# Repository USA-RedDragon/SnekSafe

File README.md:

# SnekSafe

Keep your snek safe by controlling temperature and lighting.

## Assembled v1.1 Board

## Board Renders

## Schematic

## Board Layout

## Site Images

## Parts not in the BOM that you might need

- 14AWG Silicone Wire - <https://www.amazon.com/dp/B089CRKSNN>
- Spade connectors for 14AWG - <https://www.amazon.com/dp/B08BZ972B5>
- 24AWG 4-conductor wire - <https://www.amazon.com/dp/B0BYDTCZ61>
- JST XH crimpers
- Heat shrink
- A 3d printer

## Cost

The one-off BOM cost, assuming you have spade connectors and 14AWG wire on hand is $121.25.

## On ESP32 choice

I chose the official ESP32-DevKitC-32E (ESP32-DevKitC V4) board due to quality. For some reason, on a cheaper NodeMCU ESP32S I was able to scan less WiFi networks and got a lower effective range.

## Premade Carts

A few items, such as the C13 AC cord, the C14 AC plug, and the panel mount AC outlets must be sourced on your own, as DigiKey and Mouser don't sell these commonly.

### JST XH Plug Parts

Mouser doesn't stock these: <https://www.digikey.com/short/1hzrmn3b>

### Mouser

<https://www.mouser.com/ProjectManager/ProjectDetail.aspx?AccessID=c3308da5f2>

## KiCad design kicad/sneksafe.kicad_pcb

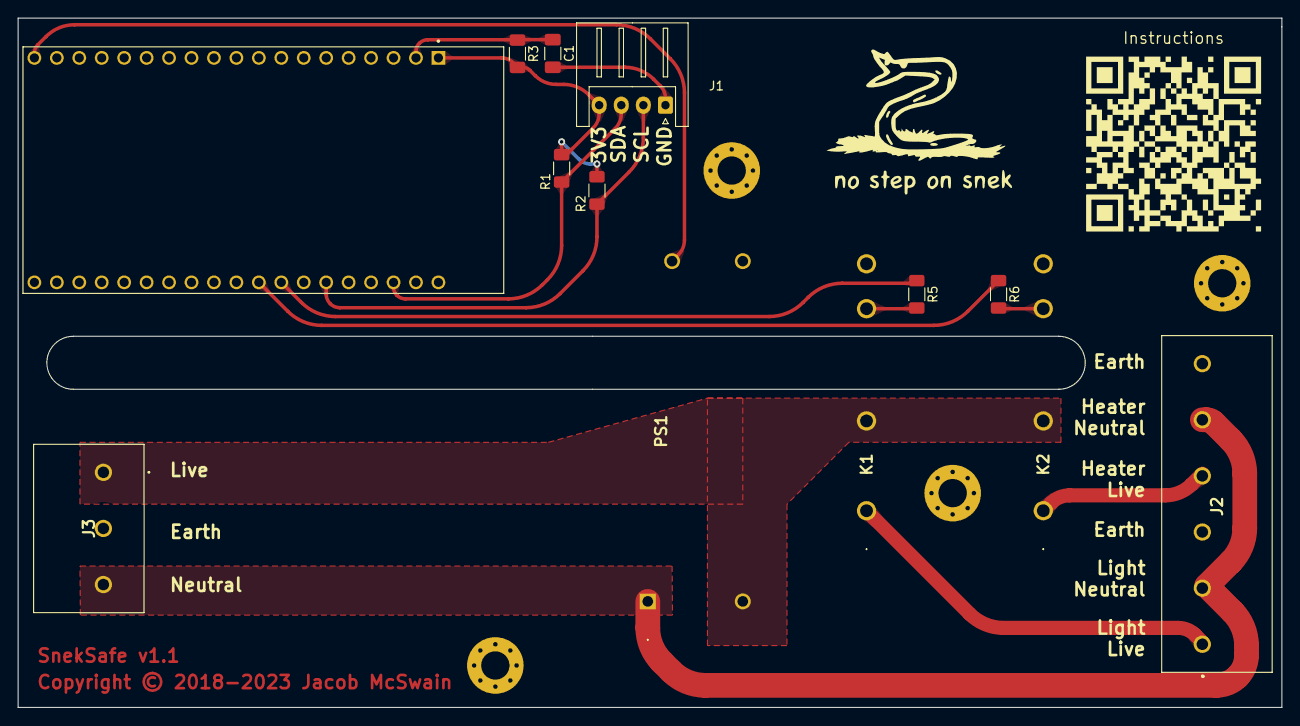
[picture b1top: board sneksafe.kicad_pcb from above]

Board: 2 copper layers, 143.0 x 78.0 mm, 18 parts (0 on the bottom side), 15 nets.

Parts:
C1: 1u; C_1206_3216Metric_Pad1.33x1.80mm_HandSolder
J1: S4B-XH-A(LF)(SN); JST_XH_S4B-XH-A_1x04_P2.50mm_Horizontal
J2: Screw_Terminal_01x06; 1713969
J3: Screw_Terminal_01x03; 1714968
K1, K2: CPC40055ST
MH1, MH2: MountingHole_3.2mm_M3_Pad_Via
MH3, MH4: MountingHole_Pad; MountingHole_3.2mm_M3_Pad_Via
PS1: RAC10E-05SK_277; RAC10E05SK277
QR*****: Instructions; rickroll
R1, R2: 2.4k; R_1206_3216Metric_Pad1.30x1.75mm_HandSolder
R3: 10k; R_1206_3216Metric_Pad1.30x1.75mm_HandSolder
R5, R6: 422; R_1206_3216Metric_Pad1.30x1.75mm_HandSolder
U1: ESP32-DEVKITC-32D; MODULE_ESP32-DEVKITC-32D

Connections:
+3.3V: J1.4, R1.2, R2.2, R3.2, U1.J2-1 (3V3)
+5V: PS1.4 (+VOUT), U1.J2-19 (EXT_5V)
AC_N_IN: J2.2, J2.5, J3.3, PS1.1 (VAC_IN_(N))
AC_P_IN: J3.1, K1.2 (AC_LOAD_2), K2.2 (AC_LOAD_2), PS1.2 (VAC_IN_(L))
Earth: MH3.1, MH4.1
GND: C1.2, J1.1, K1.4 (-_LED), K2.4 (-_LED), PS1.3 (-VOUT), U1.J2-14 (GND1), U1.J3-1 (GND3), U1.J3-7 (GND2)
HEAT_AC_P: J2.4, K2.1 (AC_LOAD_1)
HEAT_EN: R6.1, U1.J3-9 (IO18)
HEAT_LED_P: K2.3 (+_LED), R6.2
LIGHT_AC_P: J2.1, K1.1 (AC_LOAD_1)
LIGHT_EN: R5.1, U1.J3-8 (IO19)
LIGHT_LED_P: K1.3 (+_LED), R5.2
unnamed: C1.1, R3.1, U1.J2-2 (EN)
SCL: J1.3, R1.1, U1.J3-3 (IO22)
SDA: J1.2, R2.1, U1.J3-6 (IO21)

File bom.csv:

"Id";"Designator";"Footprint";"Quantity";"Designation";"Supplier and ref";
1;"R1,R2";"R_1206_3216Metric_Pad1.30x1.75mm_HandSolder";2;"2.4k";;;
2;"U1";"MODULE_ESP32-DEVKITC-32D";1;"ESP32-DEVKITC-32D";;;
3;"R3";"R_1206_3216Metric_Pad1.30x1.75mm_HandSolder";1;"10k";;;
4;"R6,R5";"R_1206_3216Metric_Pad1.30x1.75mm_HandSolder";2;"422";;;
5;"J2";"1713969";1;"Screw_Terminal_01x06";;;
6;"PS1";"RAC10E05SK277";1;"RAC10E-05SK_277";;;
7;"J1";"JST_XH_S4B-XH-A_1x04_P2.50mm_Horizontal";1;"BME280";;;
8;"K1,K2";"CPC40055ST";2;"CPC40055ST";;;
9;"C1";"C_1206_3216Metric_Pad1.33x1.80mm_HandSolder";1;"1u";;;
10;"J3";"1714968";1;"Screw_Terminal_01x03";;;

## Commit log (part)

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2023-07-07 chore(deps): update dependency vite to ^4.4.2
2023-07-07 chore(deps): update dependency semver to ^7.5.4
2023-07-10 fix(deps): update dependency primevue to ^3.30.0
2023-07-10 chore(deps): update node.js to v20.4
2023-07-11 chore(deps): update dependency vite to ^4.4.3
2023-07-11 chore(deps): update dependency prettier to v3
2023-07-14 chore(deps): update dependency vite to ^4.4.4
2023-07-14 fix(deps): update dependency primevue to ^3.30.1
2023-07-14 chore(deps): update dependency eslint to ^8.45.0
2023-07-20 chore(deps): update dependency sass to ^1.64.0
2023-07-20 fix(deps): update dependency primevue to ^3.30.2
2023-07-21 chore(deps): update dependency vite to ^4.4.6
2023-08-01 chore(deps): update dependency chart.js to ^4.3.2
2023-08-01 chore(deps): update dependency sass to ^1.64.2
2023-08-01 chore(deps): update dependency eslint to ^8.46.0
2023-08-01 chore(deps): update node.js to v20.5
2023-08-01 chore(deps): update dependency eslint-plugin-vue to ^9.16.1
2023-08-02 fix(deps): update dependency primevue to ^3.31.0
2023-08-02 chore(deps): update font awesome to ^6.4.2
2023-08-03 chore(deps): update dependency chart.js to ^4.3.3
2023-08-08 chore(deps): update dependency @rushstack/eslint-patch to ^1.3.3
2023-08-08 chore(deps): update dependency eslint-plugin-cypress to ^2.13.4
2023-08-08 chore(deps): update dependency eslint-plugin-cypress to ^2.14.0
2023-08-09 chore(deps): update dependency eslint-plugin-vue to ^9.17.0
2023-08-10 chore(deps): update dependency sass to ^1.65.1
2023-08-11 fix(deps): update dependency primevue to ^3.32.0
2023-08-11 chore(deps): update dependency eslint to ^8.47.0
2023-08-17 chore(deps): update dependency @vitejs/plugin-vue to ^4.3.1
2023-08-17 chore(deps): update dependency sass to ^1.66.0
2023-08-18 fix(deps): update dependency primevue to ^3.32.1
2023-08-19 chore(deps): update dependency sass to ^1.66.1
2023-08-21 chore(deps): update dependency @vitejs/plugin-vue to ^4.3.2
2023-08-22 chore(deps): update dependency @vitejs/plugin-vue to ^4.3.3
2023-08-24 chore(deps): update dependency chart.js to ^4.4.0
2023-08-25 fix(deps): update dependency @vuelidate/validators to ^2.0.4
2023-08-25 chore(deps): update dependency eslint to ^8.48.0
2023-08-26 fix(deps): update dependency axios to ^1.5.0
2023-08-29 chore(deps): update dependency @vitejs/plugin-vue to ^4.3.4
2023-08-31 chore(deps): update dependency platformio/platform-espressif32 to v6.4.0
2023-09-01 fix(deps): update dependency primevue to ^3.33.0
2023-09-05 chore(deps): update node.js to v20.6
2023-09-06 chore(deps): update actions/checkout action to v4
2023-09-06 chore(deps): update dependency @vue/eslint-config-prettier to v8
2023-09-08 fix(deps): update dependency primevue to ^3.34.1
2023-09-08 chore(deps): update dependency eslint to ^8.49.0
2023-09-14 chore(deps): update dependency sass to ^1.67.0
2023-09-15 chore(deps): update dependency @rushstack/eslint-patch to ^1.4.0
2023-09-20 chore(deps): update node.js to v20.7
2023-09-21 chore(deps): update dependency sass to ^1.68.0
2023-09-21 chore(deps): update dependency start-server-and-test to ^2.0.1
2023-09-22 renovate.json: add versioning to regex
2023-09-22 platformio.ini: update versioning
2023-09-22 renovate: add extract version template
2023-09-22 Kibot: don't allow blind vias
2023-09-22 kibot: fix cache
2023-09-22 kicad: fixups
2023-09-22 ci: add kibot
2023-09-22 kicad: fix DRC silkscreen clipping
2023-09-22 chore(deps): update dependency esphome/espasyncwebserver to v3.1.0
2023-09-22 chore(deps): update dependency bblanchon/arduinojson to v6.21.3
2023-09-22 chore(deps): update dependency powerbroker2/ardupid to v0.2.1
2023-09-22 chore(deps): update inti-cmnb/kibot action to v2
2023-09-22 renovate: try to fixup some odd versioning
2023-09-22 v1.1.4
2023-09-22 fix(deps): update dependency vue-router to ^4.2.5
2023-09-23 chore(deps): update dependency eslint to ^8.50.0
2023-09-26 fix(deps): update dependency primevue to ^3.35.0
2023-09-26 fix(deps): update dependency axios to ^1.5.1
2023-09-29 chore(deps): update node.js to v20.8
2023-10-01 chore(deps): update dependency @rushstack/eslint-patch to ^1.5.1
2023-10-02 chore(deps): update dependency @vitejs/plugin-vue to ^4.4.0
2023-10-03 chore(deps): update dependency vite to ^4.4.10
2023-10-05 chore(deps): update dependency vite to ^4.4.11
2023-10-06 chore(deps): update dependency eslint to ^8.51.0
2023-10-09 chore(deps): update ghcr.io/inti-cmnb/kicad7_auto:latest docker digest to 0a5e846
2023-10-10 chore(deps): update dependency sass to ^1.69.1
2023-10-10 chore(deps): update dependency sass to ^1.69.2
2023-10-11 fix(deps): update dependency primevue to ^3.36.0
2023-10-12 chore(deps): update dependency sass to ^1.69.3
2023-10-17 chore(deps): update dependency sass to ^1.69.4
2023-10-18 chore(deps): update ghcr.io/inti-cmnb/kicad7_auto:latest docker digest to 595bdcc
2023-10-18 fix(deps): update dependency primevue to ^3.37.0
2023-10-18 build(deps): bump postcss from 8.4.27 to 8.4.31 in /frontend
    Bumps [postcss](https://github.com/postcss/postcss) from 8.4.27 to 8.4.31.
    - [Release notes](https://github.com/postcss/postcss/releases)
    - [Changelog](https://github.com/postcss/postcss/blob/main/CHANGELOG.md)
    - [Commits](https://github.com/postcss/postcss/compare/8.4.27...8.4.31)
    ---
    updated-dependencies:
2023-10-20 fix(deps): update dependency vue to ^3.3.5
2023-10-20 fix(deps): update dependency vue to ^3.3.6
2023-10-20 chore(deps): update dependency eslint to ^8.52.0
2023-10-24 chore(deps): update dependency eslint-plugin-vue to ^9.18.0
2023-10-25 fix(deps): update dependency vue to ^3.3.7
2023-10-25 chore(deps): update node.js to v20.9
2023-10-26 chore(deps): update dependency sass to ^1.69.5
2023-10-26 fix(deps): update dependency primevue to ^3.38.1
2023-10-26 fix(deps): update dependency axios to ^1.6.0
2023-10-27 chore(deps): update dependency eslint-plugin-vue to ^9.18.1
2023-10-27 chore(deps): update node.js to v21
2023-11-01 fix(deps): update dependency primevue to ^3.39.0
2023-11-04 chore(deps): update dependency eslint to ^8.53.0
2023-11-05 chore(deps): update dependency start-server-and-test to ^2.0.2
2023-11-06 chore(deps): update dependency @fortawesome/vue-fontawesome to ^3.0.5
2023-11-06 fix(deps): update dependency vue to ^3.3.8
2023-11-08 chore(deps): update dependency @vitejs/plugin-vue to ^4.4.1
2023-11-09 fix(deps): update dependency primevue to ^3.40.0
2023-11-09 fix(deps): update dependency primevue to ^3.40.1
2023-11-13 chore(deps): update dependency prettier to ^3.1.0
2023-11-13 log changes in time
2023-11-13 v1.1.5
2023-11-14 fix(deps): update dependency axios to ^1.6.2
2023-11-15 Use ESPHome as the firmware
2023-11-15 release: remove needs
2023-11-15 release: use proper output for filename
2023-11-15 ci: release: fix file paths
2023-11-15 ci: release: no need for manifest
2023-12-12 firmware: add configuration options
2023-12-12 chore(deps): update dependency esphome/esphome to v2023.11.6
2023-12-14 chore(deps): update actions/upload-artifact action to v4
2023-12-20 chore(deps): update ghcr.io/inti-cmnb/kicad7_auto:latest docker digest to e245e36
2023-12-21 chore(deps): update dependency esphome/esphome to v2023.12.0
2023-12-21 chore(deps): update dependency esphome/esphome to v2023.12.1
2023-12-22 chore(deps): update dependency esphome/esphome to v2023.12.2
2023-12-22 chore(deps): update dependency esphome/esphome to v2023.12.3
2024-01-04 chore(deps): update ghcr.io/inti-cmnb/kicad7_auto:latest docker digest to 1af32f4
2024-01-09 chore(deps): update ghcr.io/inti-cmnb/kicad7_auto:latest docker digest to a0b25ce
2024-01-15 chore(deps): update dependency esphome/esphome to v2023.12.6
2024-01-17 chore(deps): update dependency esphome/esphome to v2023.12.7
2024-01-19 chore(deps): update dependency esphome/esphome to v2023.12.8
2024-01-19 ci: release-firmware: ubuntu 22.04
2024-01-19 ci: pr-kicad-diff: ubuntu 22.04
2024-01-19 ci: pr-close-kicad-delete-page: ubuntu 22.04
2024-01-19 ci: kibot: ubuntu 22.04
2024-01-19 renovate: remove useless config
2024-01-22 chore(deps): update ghcr.io/inti-cmnb/kicad7_auto:latest docker digest to 5fb7254
2024-01-23 chore(deps): update dependency esphome/esphome to v2023.12.9
2024-02-02 chore(deps): update ghcr.io/inti-cmnb/kicad7_auto:latest docker digest to ec5282f
2024-02-24 chore(deps): update esphome/build-action action to v1.9.0
2024-02-26 chore(deps): update dependency esphome/esphome to v2024
2024-02-29 chore(deps): update esphome/build-action action to v2
2024-03-06 chore(deps): update dependency esphome/esphome to v2024.2.2
2024-03-06 chore(deps): update ghcr.io/inti-cmnb/kicad7_auto:latest docker digest to 1ad631e
2024-03-22 chore(deps): update ghcr.io/inti-cmnb/kicad7_auto:latest docker digest to 35115ab
2024-03-22 chore(deps): update dependency esphome/esphome to v2024.3.0
2024-03-27 chore(deps): update dependency esphome/esphome to v2024.3.1
2024-03-31 chore(deps): update ghcr.io/inti-cmnb/kicad7_auto:latest docker digest to d6cdbe3
2024-04-01 board v1.2
2024-04-01 firmware: add rtc support
2024-04-01 Update Kiri output for PR #179
2024-04-23 chore(deps): update ghcr.io/inti-cmnb/kicad7_auto:latest docker digest to 7897248
2024-04-23 chore(deps): update ghcr.io/inti-cmnb/kicad7_auto:latest docker digest to b082a27
2024-05-03 chore(deps): update ghcr.io/inti-cmnb/kicad7_auto:latest docker digest to ab2b349
2024-05-03 chore(deps): update dependency esphome/esphome to v2024.4.2
2024-05-06 chore(deps): update ghcr.io/inti-cmnb/kicad7_auto:latest docker digest to fb37880
2024-05-15 chore(deps): update dependency esphome/esphome to v2024.5.0
2024-05-20 chore(deps): update dependency esphome/esphome to v2024.5.1
2024-05-24 chore(deps): update dependency esphome/esphome to v2024.5.3
2024-06-05 chore(deps): update dependency esphome/esphome to v2024.5.5
2024-06-19 chore(deps): update ghcr.io/inti-cmnb/kicad7_auto:latest docker digest to ccb5348
2024-06-22 firmware: set esphome ota platform
2024-06-22 chore(deps): update dependency esphome/esphome to v2024.6.1
2024-06-22 chore(deps): update esphome/build-action action to v2.0.1
2024-06-22 chore(deps): update esphome/build-action action to v3
2024-06-25 chore(deps): update dependency esphome/esphome to v2024.6.2
2024-06-27 chore(deps): update dependency esphome/esphome to v2024.6.4
2024-07-04 chore(deps): update esphome/build-action action to v3.2.0
2024-07-04 chore(deps): update dependency esphome/esphome to v2024.6.6
2024-07-31 chore(deps): update dependency esphome/esphome to v2024.7.3
2024-08-01 chore(deps): update esphome/build-action action to v3.3.0
2024-08-02 chore(deps): update esphome/build-action action to v4
2024-08-29 chore(deps): update dependency esphome/esphome to v2024.8.1
2024-09-03 chore(deps): update dependency esphome/esphome to v2024.8.3
2024-09-24 chore(deps): update dependency esphome/esphome to v2024.9.1
2024-09-25 chore(deps): update ghcr.io/inti-cmnb/kicad7_auto:latest docker digest to 933c79e
2024-09-28 chore(deps): update dependency ubuntu to v24
2025-01-18 chore(deps): update dependency esphome/esphome to v2024.12.4
2025-11-24 chore(deps): update inti-cmnb/kibot action to v2_k9
2025-12-15 chore(deps): update actions/create-release action to v1.1.4
2025-12-15 chore(deps): update actions/upload-artifact action to v4.6.2
2025-12-15 chore(deps): update actions/upload-artifact action to v5
2025-12-15 chore(deps): update actions/upload-artifact action to v6
2025-12-15 chore(deps): update esphome/build-action action to v5
2025-12-15 chore(deps): update esphome/build-action action to v6
2025-12-15 chore(config): migrate config .github/renovate.json
2026-01-15 chore(deps): update actions/upload-release-asset action to v1.0.2
2026-01-17 chore(deps): update dependency esphome/esphome to v2025

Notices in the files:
kicad/sneksafe.kicad_pcb:
Copyright © 2018-2023 Jacob McSwain
